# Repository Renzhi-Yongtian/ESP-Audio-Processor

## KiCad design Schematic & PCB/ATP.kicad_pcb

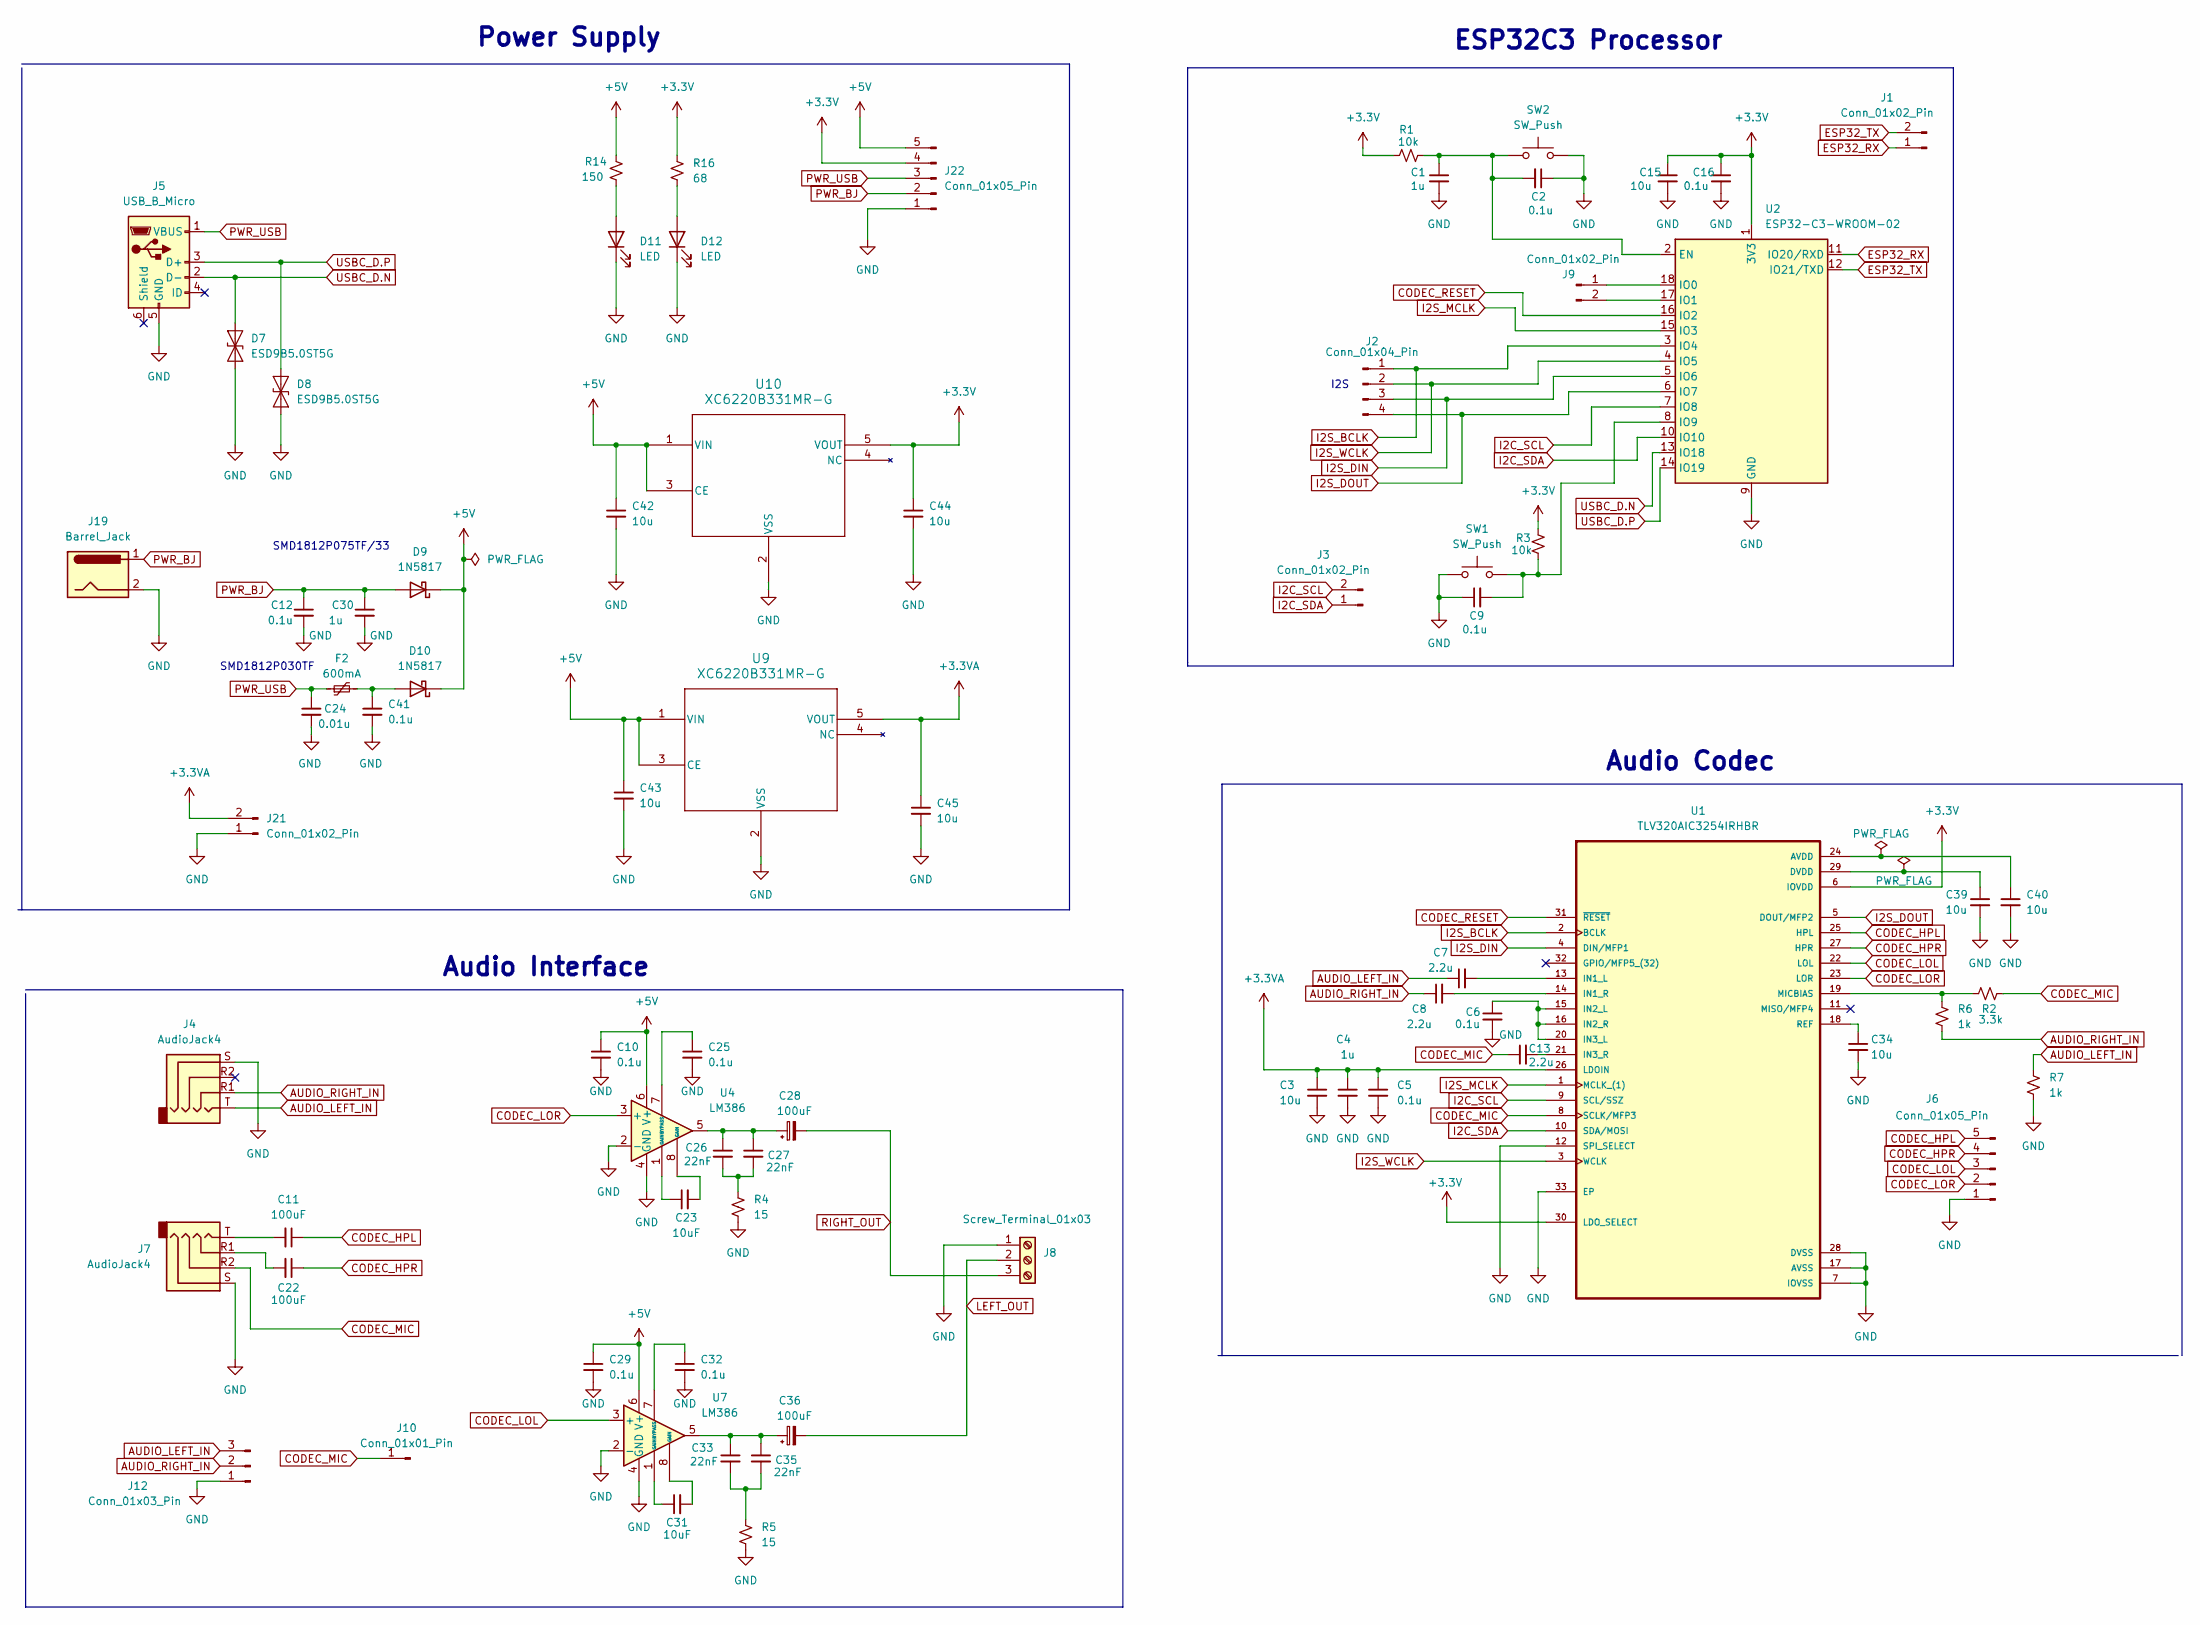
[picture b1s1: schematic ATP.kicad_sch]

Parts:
C1, C4: 1u; C_0402_1005Metric
C2, C5, C6, C9, C10, C16, C25, C29, C32, C41: 0.1u; C_0402_1005Metric
C3, C15, C34, C39, C40: 10u; C_0402_1005Metric
C7, C8, C13: 2.2u; C_0402_1005Metric
C11, C22: 100uF; C_1206_3216Metric
C12: 0.1u; C_0603_1608Metric
C23, C31: 10uF; C_0402_1005Metric
C24: 0.01u; C_0402_1005Metric
C26, C27, C33, C35: 22nF; C_0402_1005Metric
C28, C36: 100uF; C_Elec_6.3x7.7
C30: 1u; C_0603_1608Metric
C42, C43, C44, C45: 10u; C_0603_1608Metric
D7, D8: ESD9B5.0ST5G; D_SOD-923
D9, D10: 1N5817; D_SOD-123
D11, D12: LED; D_0603_1608Metric
F2: 600mA; Fuse_1812_4532Metric
J1, J3, J9, J21: Conn_01x02_Pin; PinHeader_1x02_P2.54mm_Vertical
J2: Conn_01x04_Pin; PinHeader_1x04_P2.54mm_Vertical
J4, J7: AudioJack4; Jack_3.5mm_PJ320D_Horizontal
J5: USB_B_Micro; MICRO-USB-SMD_5P-P0.65-H-F_C10418
J6, J22: Conn_01x05_Pin; PinHeader_1x05_P2.54mm_Vertical
J8: Screw_Terminal_01x03; TerminalBlock_Xinya_XY308-2.54-3P_1x03_P2.54mm_Horizontal
J10: Conn_01x01_Pin; PinHeader_1x01_P2.54mm_Vertical
J12: Conn_01x03_Pin; PinHeader_1x03_P2.54mm_Vertical
J19: Barrel_Jack; BarrelJack_CUI_PJ-063AH_Horizontal
R1, R3: 10k; R_0402_1005Metric
R2: 3.3k; R_0402_1005Metric
R4, R5: 15; R_0603_1608Metric
R6, R7: 1k; R_0402_1005Metric
R14: 150; R_0603_1608Metric
R16: 68; R_0603_1608Metric
SW1, SW2: SW_Push; SW_Push_1P1T_XKB_TS-1187A
U1: TLV320AIC3254IRHBR; IC_ADS125H01IRHBT
U2: ESP32-C3-WROOM-02
U4, U7: LM386; SOP-8_3.9x4.9mm_P1.27mm
U9, U10: XC6220B331MR-G; SOT-25_TOR

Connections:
+3.3V: C15.1, C16.1, C44.1, J22.4, R1.1, R3.1, R16.1, U1.6 (IOVDD), U1.30 (LDO_SELECT), U2.1 (3V3), U10.5 (VOUT)
+3.3VA: C3.1, C4.1, C5.1, C45.1, J21.2, U1.26 (LDOIN), U9.5 (VOUT)
+5V: C10.1, C29.1, C42.1, C43.1, D9.1 (K), D10.1 (K), J22.5, R14.1, U4.6 (V+), U7.6 (V+), U9.1 (VIN), U9.3 (CE), U10.1 (VIN), U10.3 (CE)
AUDIO_LEFT_IN: C7.1, J4.T, J12.3, R7.1
AUDIO_RIGHT_IN: C8.1, J4.R1, J12.2, R6.2
CODEC_HPL: C11.1, J6.5, U1.25 (HPL)
CODEC_HPR: C22.1, J6.4, U1.27 (HPR)
CODEC_LOL: J6.3, U1.22 (LOL), U7.3 (+)
CODEC_LOR: J6.2, U1.23 (LOR), U4.3 (+)
CODEC_MIC: C13.1, J7.R2, J10.1, R2.2, U1.8 (SCLK/MFP3)
CODEC_RESET: U1.31 (~RESET), U2.16 (IO2)
ESP32_RX: J1.1, U2.11 (IO20/RXD)
ESP32_TX: J1.2, U2.12 (IO21/TXD)
GND: C1.2, C2.1, C3.2, C4.2, C5.2, C6.2, C9.1, C10.2, C12.2, C15.2, C16.2, C24.2, C25.2, C29.2, C30.2, C32.2, C34.2, C39.2, C40.2, C41.2, C42.2, C43.2, C44.2, C45.2, D7.1 (A1), D8.1 (A1), D11.1 (K), D12.1 (K), J4.S, J5.5 (GND), J6.1, J7.S, J8.1, J12.1, J19.2, J21.1, J22.1, R4.2, R5.2, R7.2, SW1.2, SW2.2, U1.7 (IOVSS), U1.12 (SPI_SELECT), U1.17 (AVSS), U1.28 (DVSS), U1.33 (EP), U2.9 (GND), U2.19 (GND), U4.2 (-), U4.4 (GND), U7.2 (-), U7.4 (GND), U9.2 (VSS), U10.2 (VSS)
I2C_SCL: J3.2, U1.9 (SCL/SSZ), U2.7 (IO8)
I2C_SDA: J3.1, U1.10 (SDA/MOSI), U2.10 (IO10)
I2S_BCLK: J2.1, U1.2 (BCLK), U2.3 (IO4)
I2S_DIN: J2.3, U1.4 (DIN/MFP1), U2.5 (IO6)
I2S_DOUT: J2.4, U1.5 (DOUT/MFP2), U2.6 (IO7)
I2S_MCLK: U1.1 (MCLK_(1)), U2.15 (IO3)
I2S_WCLK: J2.2, U1.3 (WCLK), U2.4 (IO5)
LEFT_OUT: C36.2, J8.2
unnamed: C11.2, J7.T
unnamed: C22.2, J7.R1
unnamed: C23.1, U4.1 (GAIN)
unnamed: C23.2, U4.8 (GAIN)
unnamed: C26.1, C27.1, C28.1, U4.5
unnamed: C26.2, C27.2, R4.1
unnamed: C31.1, U7.1 (GAIN)
unnamed: C31.2, U7.8 (GAIN)
unnamed: C33.1, C35.1, C36.1, U7.5
unnamed: C33.2, C35.2, R5.1
unnamed: C41.1, D10.2 (A), F2.2
unnamed: D11.2 (A), R14.2
unnamed: D12.2 (A), R16.2
unnamed: J9.1, U2.18 (IO0)
unnamed: J9.2, U2.17 (IO1)
unnamed: C40.1, U1.24 (AVDD)
unnamed: C39.1, U1.29 (DVDD)
unnamed: C7.2, U1.13 (IN1_L)
unnamed: C8.2, U1.14 (IN1_R)
unnamed: C6.1, U1.15 (IN2_L), U1.16 (IN2_R), U1.20 (IN3_L)
unnamed: C13.2, U1.21 (IN3_R)
unnamed: R2.1, R6.1, U1.19 (MICBIAS)
unnamed: C34.1, U1.18 (REF)
unnamed: C1.1, C2.2, R1.2, SW2.1, U2.2 (EN)
unnamed: C9.2, R3.2, SW1.1, U2.8 (IO9)
unnamed: C25.1, U4.7 (BYPASS)
unnamed: C32.1, U7.7 (BYPASS)
PWR_BJ: C12.1, C30.1, D9.2 (A), J19.1, J22.2
PWR_USB: C24.1, F2.1, J5.1 (VBUS), J22.3
RIGHT_OUT: C28.2, J8.3
USBC_D.N: D7.2 (A2), J5.2 (D-), U2.13 (IO18)
USBC_D.P: D8.2 (A2), J5.3 (D+), U2.14 (IO19)

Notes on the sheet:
ESP32C3 Processor
Audio Interface
I2S
SMD1812P075TF/33
Power Supply
SMD1812P030TF
Audio Codec

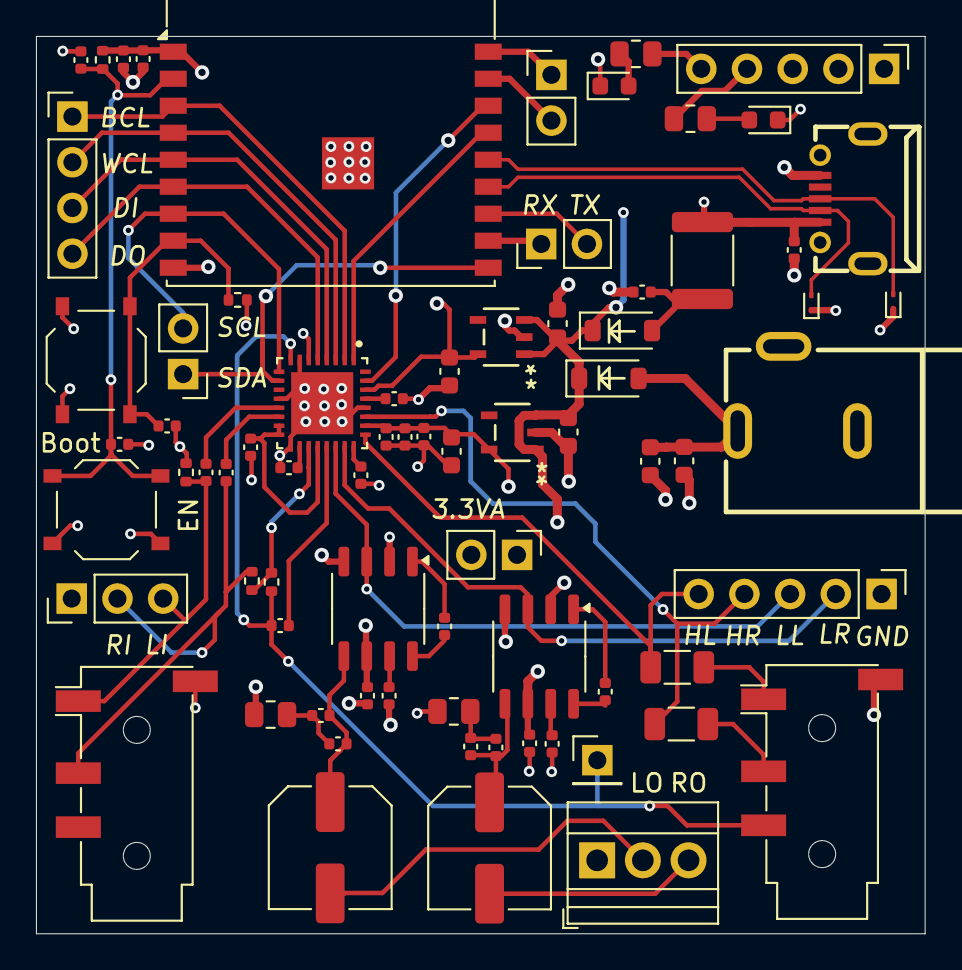
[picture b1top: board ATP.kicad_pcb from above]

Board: 4 copper layers, 49.4 x 49.9 mm, 75 parts (0 on the bottom side), 54 nets.

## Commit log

2025-01-26 KiCAD PCB Design
2025-03-11 uploaded source code
